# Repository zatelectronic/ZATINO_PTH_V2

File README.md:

<div align="center">

# ZATINO V2 PTH

**Placa de desenvolvimento compatível com Arduino Uno, com componentes através-furo (PTH), programação USB-C via módulo FT232RL**

</div>

---

## 📋 Índice

- [ZATINO V2 PTH](#zatino-v2-pth)
  - [📋 Índice](#-índice)
  - [Visão Geral](#visão-geral)
  - [Renders 3D](#renders-3d)
  - [Diferenças em relação ao ZATINO SMD V2](#diferenças-em-relação-ao-zatino-smd-v2)
  - [Funcionalidades](#funcionalidades)
  - [Especificações Técnicas](#especificações-técnicas)
  - [Lista de Materiais](#lista-de-materiais)
  - [Arquitetura de Alimentação](#arquitetura-de-alimentação)
  - [Compatibilidade de Pinos](#compatibilidade-de-pinos)
  - [Estrutura do Repositório](#estrutura-do-repositório)
  - [Como Usar](#como-usar)
    - [Abrindo no KiCad](#abrindo-no-kicad)
    - [Programando a Placa](#programando-a-placa)
    - [Dica de Montagem](#dica-de-montagem)
  - [Sobre](#sobre)

---

## Visão Geral

**ZATINO V2 PTH** é uma placa de desenvolvimento personalizada, compatível com Arduino Uno, projetada pela **ZAT ELECTRONIC** utilizando o **KICAD 10**. Diferente da versão SMD, esta placa utiliza exclusivamente **componentes através-furo (PTH — Pin Through Hole)**, tornando-a ideal para montagem manual, prototipagem, aprendizado e laboratórios maker.

O microcontrolador principal é o clássico **ATmega328P-PU** no encapsulamento **DIP-28**, encaixado diretamente na placa. A programação é feita via **USB-C** através do módulo **FT232RL**, conectado a um conector fêmea de 6 pinos na borda da placa.

> 💡 Esta placa mantém **total compatibilidade de pinos com o Arduino Uno R3**, permitindo o uso de shields e bibliotecas existentes sem qualquer modificação.

---

## Renders 3D

<div align="center">

*Vista superior — componentes PTH, LEDs coloridos e serigrafia*

<br/>

*Vista isométrica — ATmega328P-PU DIP-28, módulo FT232RL USB-C e montagem geral*

</div>

---

## Diferenças em relação ao ZATINO SMD V2

| Característica | ZATINO V2 PTH | ZATINO SMD V2 |
|----------------|--------------|--------------|
| **Microcontrolador** | ATmega328P-PU (DIP-28) | ATmega328PB-AU (TQFP-32) |
| **Tipo de componentes** | Através-furo (PTH) | Montagem superficial (SMD) |
| **LEDs** | 5mm PTH (vermelho e azul) | SMD 1210 |
| **Resistores** | Axial 0,5W PTH | SMD 1206 |
| **Capacitores** | Eletrolítico + Disco cerâmico PTH | SMD 0805 |
| **Cristal** | PTH HC-49 | SMD HC-49/SD |
| **Montagem** | Manual / Soldagem fácil | Reflow / Soldagem SMD |
| **Público alvo** | Iniciantes, makers, laboratório | Produção, compacto, profissional |

---

## Funcionalidades

- ✅ **ATmega328P-PU** — encapsulamento DIP-28 PTH, 100% compatível com Arduino Uno
- ✅ **Programação via USB-C** pelo módulo FT232RL (conector plugável)
- ✅ **Duplo regulador de tensão** — 5V (AMS1117-5.0) e 3,3V (AMS1117-3.3)
- ✅ **Proteção contra inversão de polaridade** via diodo 1N4007 PTH na entrada de alimentação
- ✅ **Oscilador a cristal de 16 MHz** (encapsulamento PTH HC-49)
- ✅ **Pinout completo Arduino Uno R3** — conectores Digital, Analógico, Alimentação e ICSP
- ✅ **LED vermelho e LED azul** (5mm PTH) para sinalização de status
- ✅ **Botão de reset tátil** (THT 6×6×5 mm)
- ✅ **Entrada de alimentação Barrel Jack (P4)** com chave integrada
- ✅ **Todos os componentes PTH** — ideal para soldagem manual e aprendizado
- ✅ **Projetado com KICAD 10** — EDA totalmente open source
- ✅ **Logotipo Open Source Hardware** na PCB

---

## Especificações Técnicas

| Parâmetro | Valor |
|-----------|-------|
| **Microcontrolador** | ATmega328P-PU (DIP-28) |
| **Velocidade de Clock** | 16 MHz (cristal externo PTH) |
| **Tensão de Operação** | 5V |
| **Tensão de Entrada** | 7–12V (Barrel Jack P4) |
| **Saída 3,3V** | AMS1117-3.3 (até 800mA) |
| **Regulador 5V** | AMS1117-5.0 |
| **Interface USB** | USB-C via módulo FT232RL |
| **Pinos Digital I/O** | 14 (D0–D13), PWM em D3, D5, D6, D9, D10, D11 |
| **Entradas Analógicas** | 6 (A0–A5) |
| **Memória Flash** | 32 KB (ATmega328P) |
| **SRAM** | 2 KB |
| **EEPROM** | 1 KB |
| **Tipo de Montagem** | PTH — Através-furo |
| **Ferramenta de Projeto** | KICAD 10.0 |
| **Versão da PCB** | V2 — 2025 |
| **Fator de Forma** | Compatível com Arduino Uno R3 |

---

## Lista de Materiais

| Ref | Componente | Valor / Parte | Encapsulamento |
|-----|-----------|--------------|----------------|
| MICROCONTROLADOR1 | Microcontrolador | ATmega328P-PU | DIP-28 PTH |
| REGULADOR_5V1 | Regulador de Tensão 5V | AMS1117-5.0 | SOT-223 |
| REGULADOR_3V3 | Regulador de Tensão 3,3V | AMS1117-3.3 | SOT-223 |
| 16MHZ1 | Oscilador a Cristal | 16 MHz | HC-49 PTH |
| BARRA_DE_PINO2 | Conector FTDI | FT232RL USB-C | Fêmea 6 pinos 2,54mm |
| A2 | Referência de Pinout | Arduino Uno R3 | — |
| D1 | Diodo Retificador | 1N4007 | PTH Axial |
| L1 | LED de Status | LED 5mm Vermelho | PTH 5mm |
| L2 | LED de Status | LED 5mm Azul | PTH 5mm |
| R1 | Resistor de LED | 470Ω | Axial 0,5W PTH |
| R2 | Resistor de LED | 220Ω | Axial 0,5W PTH |
| R3 | Resistor de Pull-up | 10KΩ | Axial 0,5W PTH |
| C1, C2, C3 | Capacitores Eletrolíticos | 10µF / 50V | PTH 5×11mm |
| C4, C5 | Capacitores de Cristal | 22pF | Disco Cerâmico PTH |
| C6, C7 | Capacitores de Bypass | 100nF | Disco Cerâmico PTH |
| CONECTOR1 | Conector de Alimentação DC | Barrel Jack P4 | PTH Horizontal |
| BARRA_DE_PINO1 | Conector Auxiliar | 2 terminais | PTH 2,54mm |
| TACTIL_SWITCH1 | Botão de Reset | 6×6×5mm | THT Tátil |
| TP1 | Ponto de Teste | — | PTH |

---

## Arquitetura de Alimentação

```
VIN (Barrel Jack P4)
        │
    [1N4007]  ← Proteção contra inversão de polaridade
        │
   ┌────┴────┐
   │         │
[AMS1117-5.0]  [AMS1117-3.3]
   │         │
  +5V       +3,3V
   │
[ATmega328P-PU DIP-28]
   │
[FT232RL USB-C] ← UART TX/RX + DTR (auto-reset)
```

A placa suporta duas fontes de alimentação:
- **Barrel Jack (P4)** — entrada de 7 a 12V DC, regulada para 5V e 3,3V internamente
- **USB-C via módulo FT232RL** — 5V direto do USB, alimentando o rail VCC quando conectado

---

## Compatibilidade de Pinos

A placa expõe o **pinout completo do Arduino Uno R3**:

| Conector | Pinos |
|----------|-------|
| Digital (PWM) | D0–D13, com PWM em ~3, ~5, ~6, ~9, ~10, ~11 |
| Entradas Analógicas | A0–A5 |
| Alimentação | VIN, 5V, 3V3, GND, AREF, IOREF, RESET |
| ICSP | MISO, MOSI, SCK, RESET, VCC, GND |
| UART (FT232RL) | TX, RX (via conector BARRA_DE_PINO2) |
| I2C | SDA (A4), SCL (A5) |

---

## Estrutura do Repositório

```
ZATINO_PTH_V2/
├── ZATINO_PTH_V2.kicad_pro       # Arquivo de projeto KiCad
├── ZATINO_PTH_V2.kicad_sch       # Esquemático (KICAD 10)
├── ZATINO_PTH_V2.kicad_pcb       # Layout da PCB (KICAD 10)
├── ZATINO_PTH_V2.kicad_prl       # Configurações locais do projeto
├── packages3D/                   # Modelos 3D arquivados (STEP / WRL)
│   ├── atmega328.STEP
│   ├── AMS1117_3V3_axisY.step
│   ├── AMS1117_5V_axisY.step
│   ├── Waveshare_FT232RL_USB-C.step
│   ├── Cristal 16MHz.STEP
│   ├── LED 5mm Red.step
│   ├── LED 5mm Blue.step
│   ├── Diodo 1N4007.STEP
│   └── ...
├── fp-info-cache                 # Cache de footprints
├── fabrication-toolkit-options.json
├── imagem_1.png                  # Render superior da PCB
├── imagem_2.png                  # Render isométrico da PCB
└── README.md
```

---

## Como Usar

### Abrindo no KiCad

1. Instale o **KICAD 10.0** ou superior
2. Clone este repositório:
   ```bash
   git clone https://github.com/seu-usuario/ZATINO_PTH_V2.git
   ```
3. Abra o arquivo `ZATINO_PTH_V2.kicad_pro` no KiCad

### Programando a Placa

1. Encaixe o **módulo FT232RL USB-C** no conector de 6 pinos (`BARRA_DE_PINO2`)
2. Conecte via USB-C ao computador
3. Abra o **Arduino IDE** ou **PlatformIO**
4. Selecione a placa: **Arduino Uno**
5. Selecione a porta COM correta e faça o upload do sketch

### Dica de Montagem

> 🔧 Por ser totalmente PTH, a placa pode ser soldada com ferro de solda convencional. Recomenda-se seguir a ordem: componentes baixos primeiro (resistores, diodo, cristal), depois capacitores, reguladores, soquete DIP-28 e por último os conectores e LEDs.

---

## Sobre

<div align="center">

Projetado por **ZAT ELECTRONIC**

*ZATINO V2 PTH — 2025*

</div>

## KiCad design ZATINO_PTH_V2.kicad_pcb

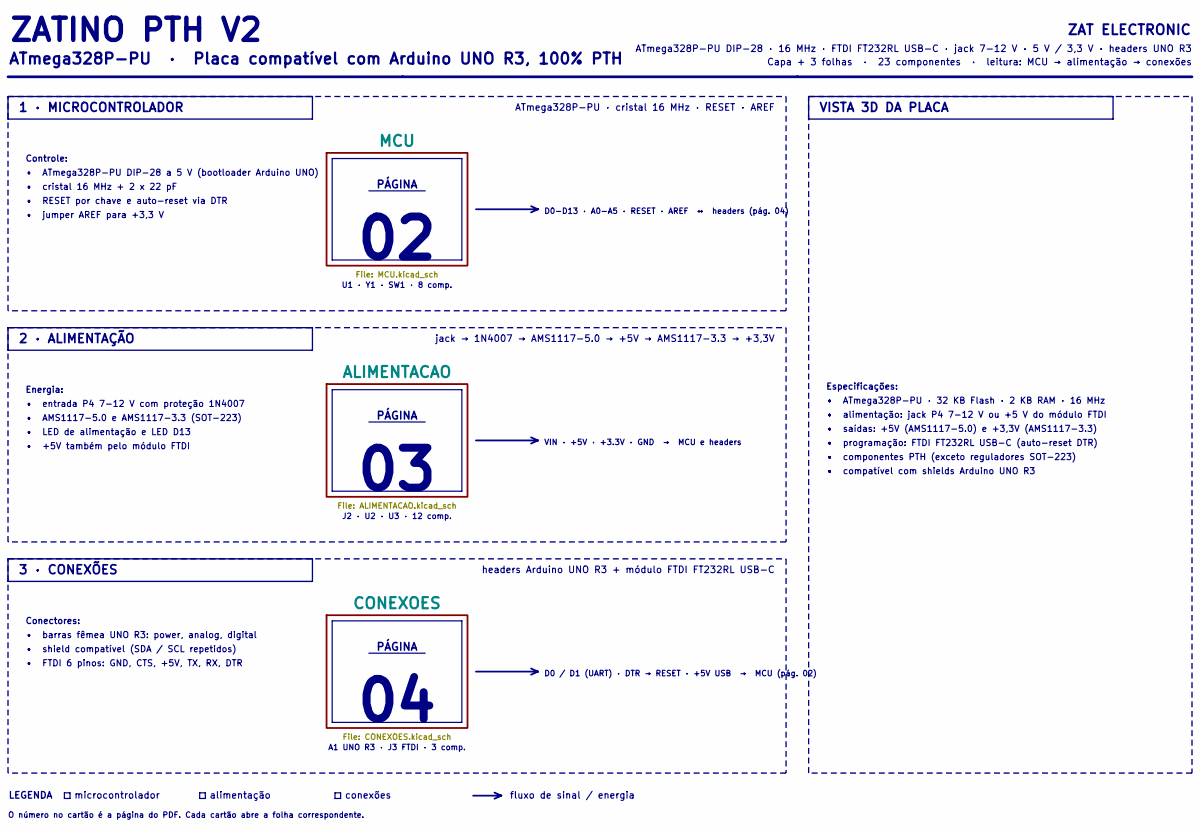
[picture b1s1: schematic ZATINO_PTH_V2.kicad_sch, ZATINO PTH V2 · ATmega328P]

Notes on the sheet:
ZAT ELECTRONIC
Especificações:
• RESET por chave e auto-reset via DTR
D0 / D1 (UART) · DTR → RESET · +5V USB → MCU (pág. 02)
• shield compatível (SDA / SCL repetidos)
J2 · U2 · U3 · 12 comp.
PÁGINA
3 · CONEXÕES
ATmega328P-PU · cristal 16 MHz · RESET · AREF
fluxo de sinal / energia
• +5V também pelo módulo FTDI
conexões
microcontrolador
LEGENDA
Controle:
• barras fêmea UNO R3: power, analog, digital
• jumper AREF para +3,3 V
• LED de alimentação e LED D13
A1 UNO R3 · J3 FTDI · 3 comp.
• cristal 16 MHz + 2 x 22 pF
O número no cartão é a página do PDF. Cada cartão abre a folha correspondente.
• ATmega328P-PU · 32 KB Flash · 2 KB RAM · 16 MHz
• AMS1117-5.0 e AMS1117-3.3 (SOT-223)
ATmega328P-PU · Placa compatível com Arduino UNO R3, 100% PTH
alimentação
• FTDI 6 pinos: GND, CTS, +5V, TX, RX, DTR
• componentes PTH (exceto reguladores SOT-223)
• saídas: +5V (AMS1117-5.0) e +3,3V (AMS1117-3.3)
1 · MICROCONTROLADOR
D0-D13 · A0-A5 · RESET · AREF ↔ headers (pág. 04)
ATmega328P-PU DIP-28 · 16 MHz · FTDI FT232RL USB-C · jack 7-12 V · 5 V / 3,3 V · headers UNO R3
Capa + 3 folhas · 23 componentes · leitura: MCU → alimentação → conexões
• programação: FTDI FT232RL USB-C (auto-reset DTR)
• alimentação: jack P4 7-12 V ou +5 V do módulo FTDI
VISTA 3D DA PLACA
Conectores:
Energia:
U1 · Y1 · SW1 · 8 comp.
ZATINO PTH V2
VIN · +5V · +3.3V · GND → MCU e headers

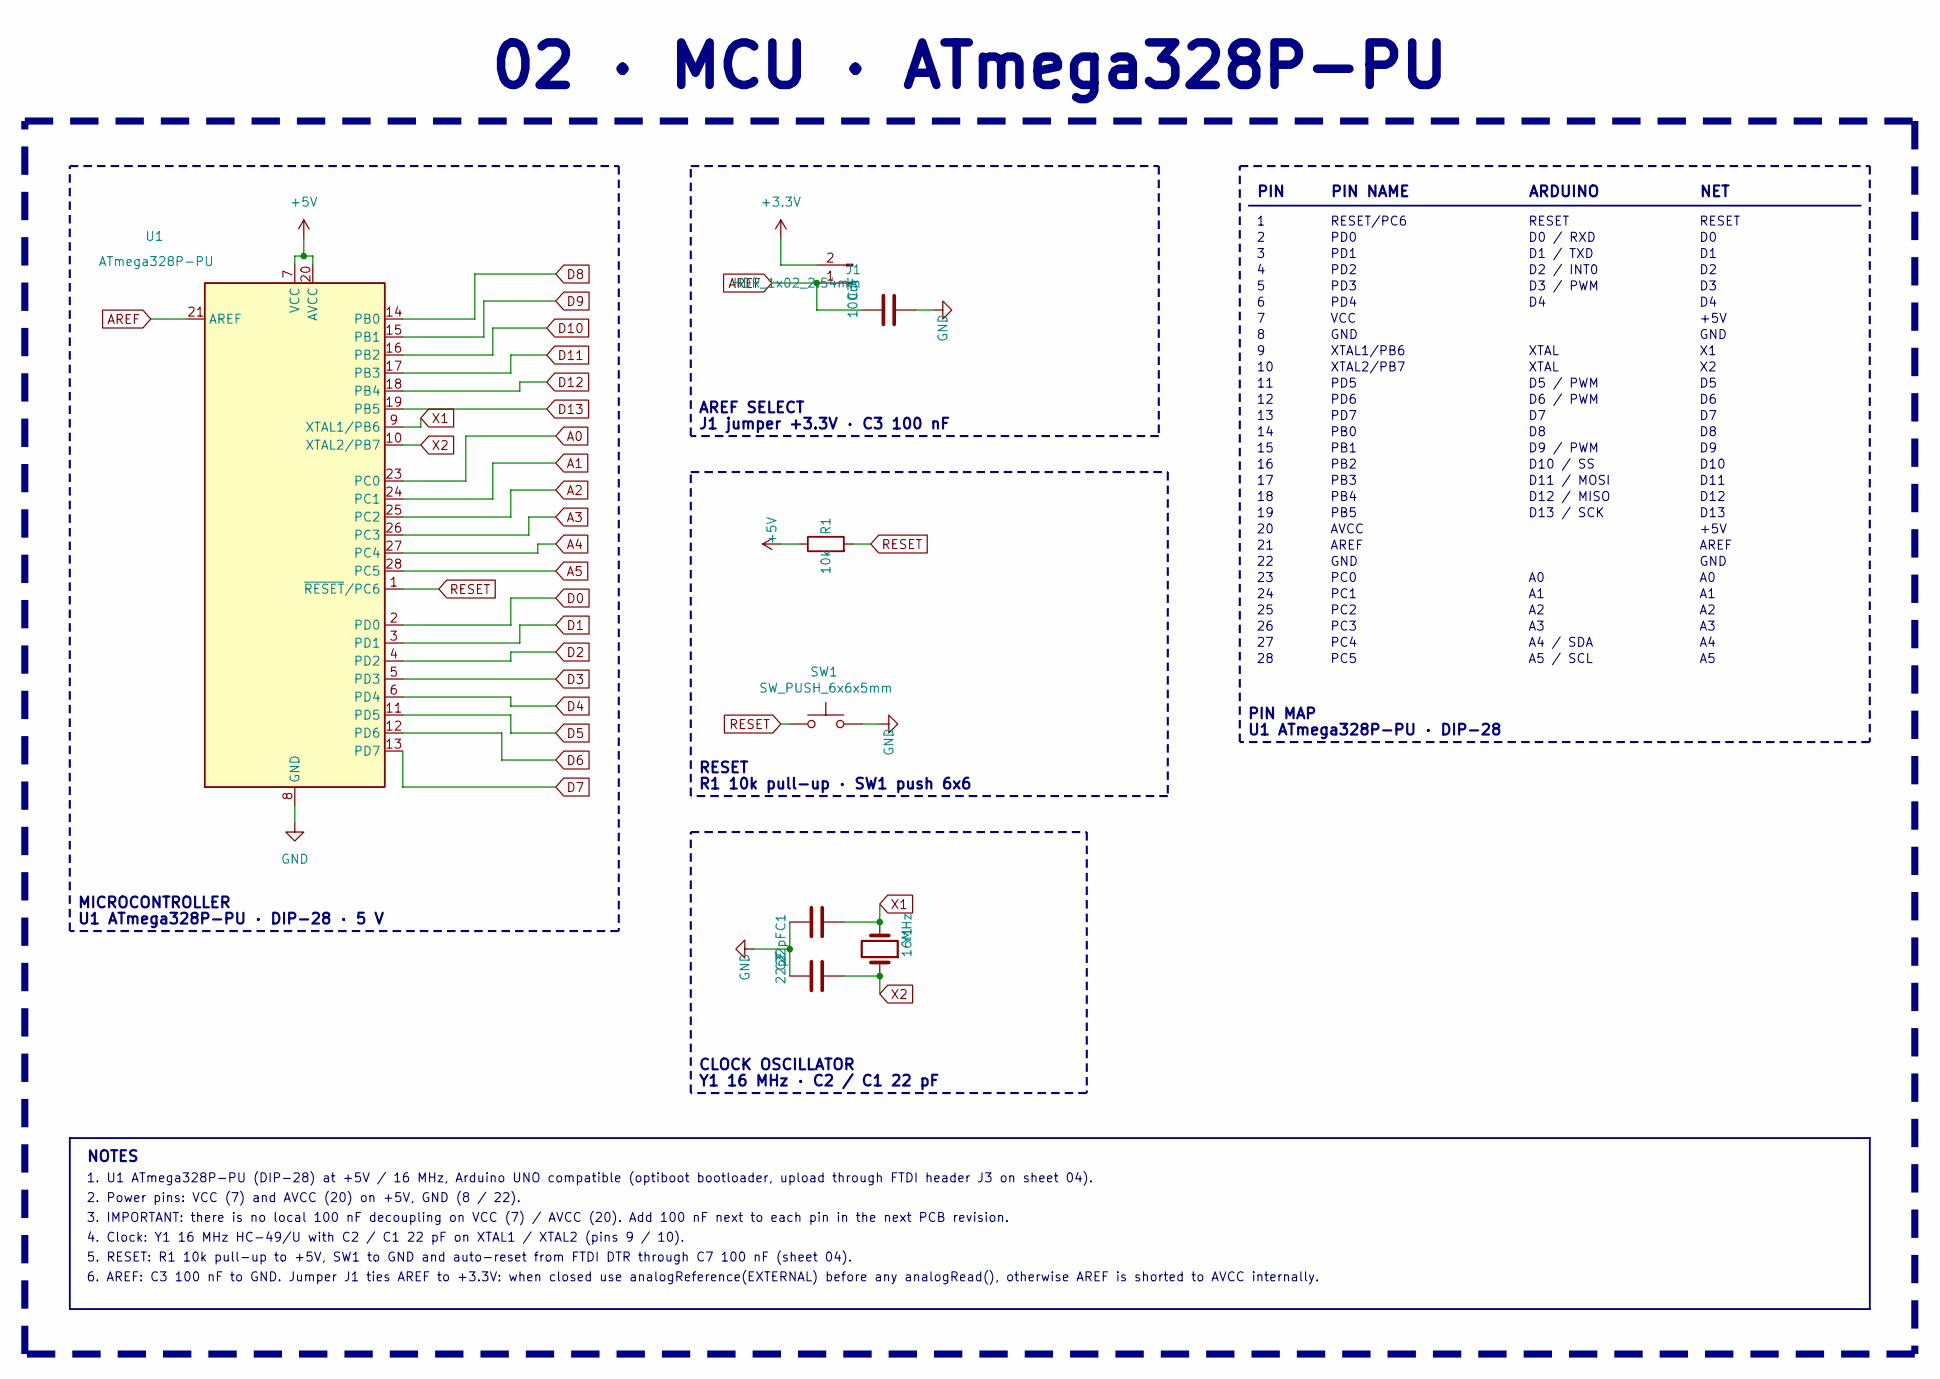
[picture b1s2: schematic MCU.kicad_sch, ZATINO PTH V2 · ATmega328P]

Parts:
C1, C2: 22pF; C_Disc_D3.0mm_W1.6mm_P2.50mm_22pF
C3: 100nF; C_Disc_D3.0mm_W2.0mm_P2.50mm_100nF
J1: HDR_1x02_2.54mm; PinHeader_1x02_P2.54mm_Vertical
R1: 10k; R_Axial_DIN0204_L3.6mm_D1.6mm_P7.62mm_Horizontal_10K
SW1: SW_PUSH_6x6x5mm; SW_PUSH_6mm_H5mm
U1: ATmega328P-PU; DIP-28_W7.62mm_ATmega328P-PU
Y1: 16MHz; Crystal_HC18-U_Vertical_16MHz

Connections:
+3.3V: J1.2; also elsewhere on the board
+5V: R1.1, U1.7 (VCC), U1.20 (AVCC); also elsewhere on the board
A0: U1.23 (PC0); also elsewhere on the board
A1: U1.24 (PC1); also elsewhere on the board
A2: U1.25 (PC2); also elsewhere on the board
A3: U1.26 (PC3); also elsewhere on the board
A4: U1.27 (PC4); also elsewhere on the board
A5: U1.28 (PC5); also elsewhere on the board
AREF: C3.2, J1.1, U1.21 (AREF); also elsewhere on the board
D0: U1.2 (PD0); also elsewhere on the board
D1: U1.3 (PD1); also elsewhere on the board
D2: U1.4 (PD2); also elsewhere on the board
D3: U1.5 (PD3); also elsewhere on the board
D4: U1.6 (PD4); also elsewhere on the board
D5: U1.11 (PD5); also elsewhere on the board
D6: U1.12 (PD6); also elsewhere on the board
D7: U1.13 (PD7); also elsewhere on the board
D8: U1.14 (PB0); also elsewhere on the board
D9: U1.15 (PB1); also elsewhere on the board
D10: U1.16 (PB2); also elsewhere on the board
D11: U1.17 (PB3); also elsewhere on the board
D12: U1.18 (PB4); also elsewhere on the board
D13: U1.19 (PB5); also elsewhere on the board
GND: C1.2, C2.2, C3.1, SW1.2, U1.8 (GND), U1.22 (GND); also elsewhere on the board
RESET: R1.2, SW1.1, U1.1 (~RESET/PC6); also elsewhere on the board
X1: C1.1, U1.9 (XTAL1/PB6), Y1.2
X2: C2.1, U1.10 (XTAL2/PB7), Y1.1

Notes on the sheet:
GND
D13
AREF SELECT
PD4
D6 / PWM
D3 / PWM
AREF
PD2
PD1
RESET
CLOCK OSCILLATOR
PD7
RESET/PC6
XTAL1/PB6
D2 / INT0
A5 / SCL
D12 / MISO
02 · MCU · ATmega328P-PU
D5 / PWM
+5V
XTAL2/PB7
D9 / PWM
XTAL
3. IMPORTANT: there is no local 100 nF decoupling on VCC (7) / AVCC (20). Add 100 nF next to each pin in the next PCB revision.
PB3
PC4
PIN NAME
PIN MAP
PC3
5. RESET: R1 10k pull-up to +5V, SW1 to GND and auto-reset from FTDI DTR through C7 100 nF (sheet 04).
2. Power pins: VCC (7) and AVCC (20) on +5V, GND (8 / 22).
D13 / SCK
PC1
A4 / SDA
NOTES
ARDUINO
VCC
D10
PD6
D1 / TXD

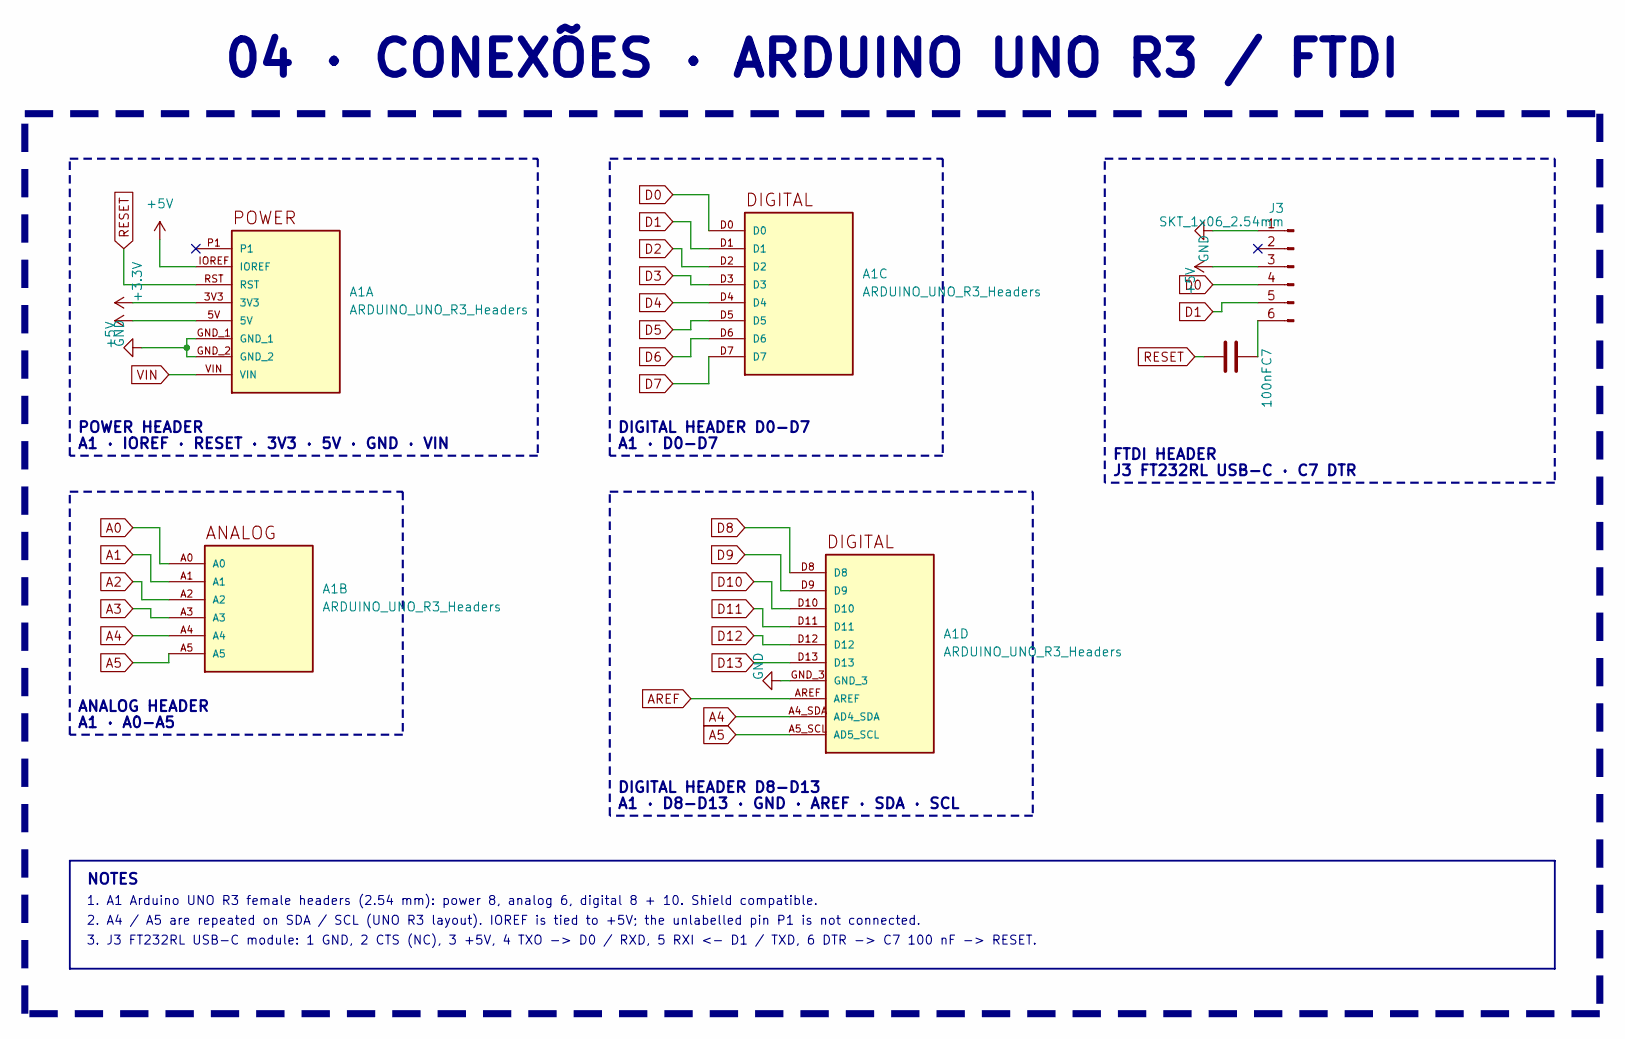
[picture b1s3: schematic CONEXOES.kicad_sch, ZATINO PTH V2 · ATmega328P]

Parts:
A1: ARDUINO_UNO_R3_Headers
C7: 100nF; C_Disc_D3.0mm_W2.0mm_P2.50mm_100nF
J3: SKT_1x06_2.54mm; PinSocket_1x06_P2.54mm_Vertical_FT232RL_USB-C

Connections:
+3.3V: A1.3V3; also elsewhere on the board
+5V: A1.5V, A1.IOREF, J3.3; also elsewhere on the board
A0: A1.A0; also elsewhere on the board
A1: A1.A1; also elsewhere on the board
A2: A1.A2; also elsewhere on the board
A3: A1.A3; also elsewhere on the board
A4: A1.A4, A1.A4_SDA (AD4_SDA); also elsewhere on the board
A5: A1.A5, A1.A5_SCL (AD5_SCL); also elsewhere on the board
AREF: A1.AREF; also elsewhere on the board
D0: A1.D0, J3.4; also elsewhere on the board
D1: A1.D1, J3.5; also elsewhere on the board
D2: A1.D2; also elsewhere on the board
D3: A1.D3; also elsewhere on the board
D4: A1.D4; also elsewhere on the board
D5: A1.D5; also elsewhere on the board
D6: A1.D6; also elsewhere on the board
D7: A1.D7; also elsewhere on the board
D8: A1.D8; also elsewhere on the board
D9: A1.D9; also elsewhere on the board
D10: A1.D10; also elsewhere on the board
D11: A1.D11; also elsewhere on the board
D12: A1.D12; also elsewhere on the board
D13: A1.D13; also elsewhere on the board
GND: A1.GND_1, A1.GND_2, A1.GND_3, J3.1; also elsewhere on the board
unnamed: C7.1, J3.6
RESET: A1.RST, C7.2; also elsewhere on the board
VIN: A1.VIN; also elsewhere on the board

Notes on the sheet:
POWER HEADER
J3 FT232RL USB-C · C7 DTR
A1 · D0-D7
DIGITAL HEADER D8-D13
ANALOG HEADER
DIGITAL HEADER D0-D7
FTDI HEADER
A1 · D8-D13 · GND · AREF · SDA · SCL
A1 · IOREF · RESET · 3V3 · 5V · GND · VIN
A1 · A0-A5
04 · CONEXÕES · ARDUINO UNO R3 / FTDI
1. A1 Arduino UNO R3 female headers (2.54 mm): power 8, analog 6, digital 8 + 10. Shield compatible.
NOTES
3. J3 FT232RL USB-C module: 1 GND, 2 CTS (NC), 3 +5V, 4 TXO -> D0 / RXD, 5 RXI <- D1 / TXD, 6 DTR -> C7 100 nF -> RESET.
2. A4 / A5 are repeated on SDA / SCL (UNO R3 layout). IOREF is tied to +5V; the unlabelled pin P1 is not connected.

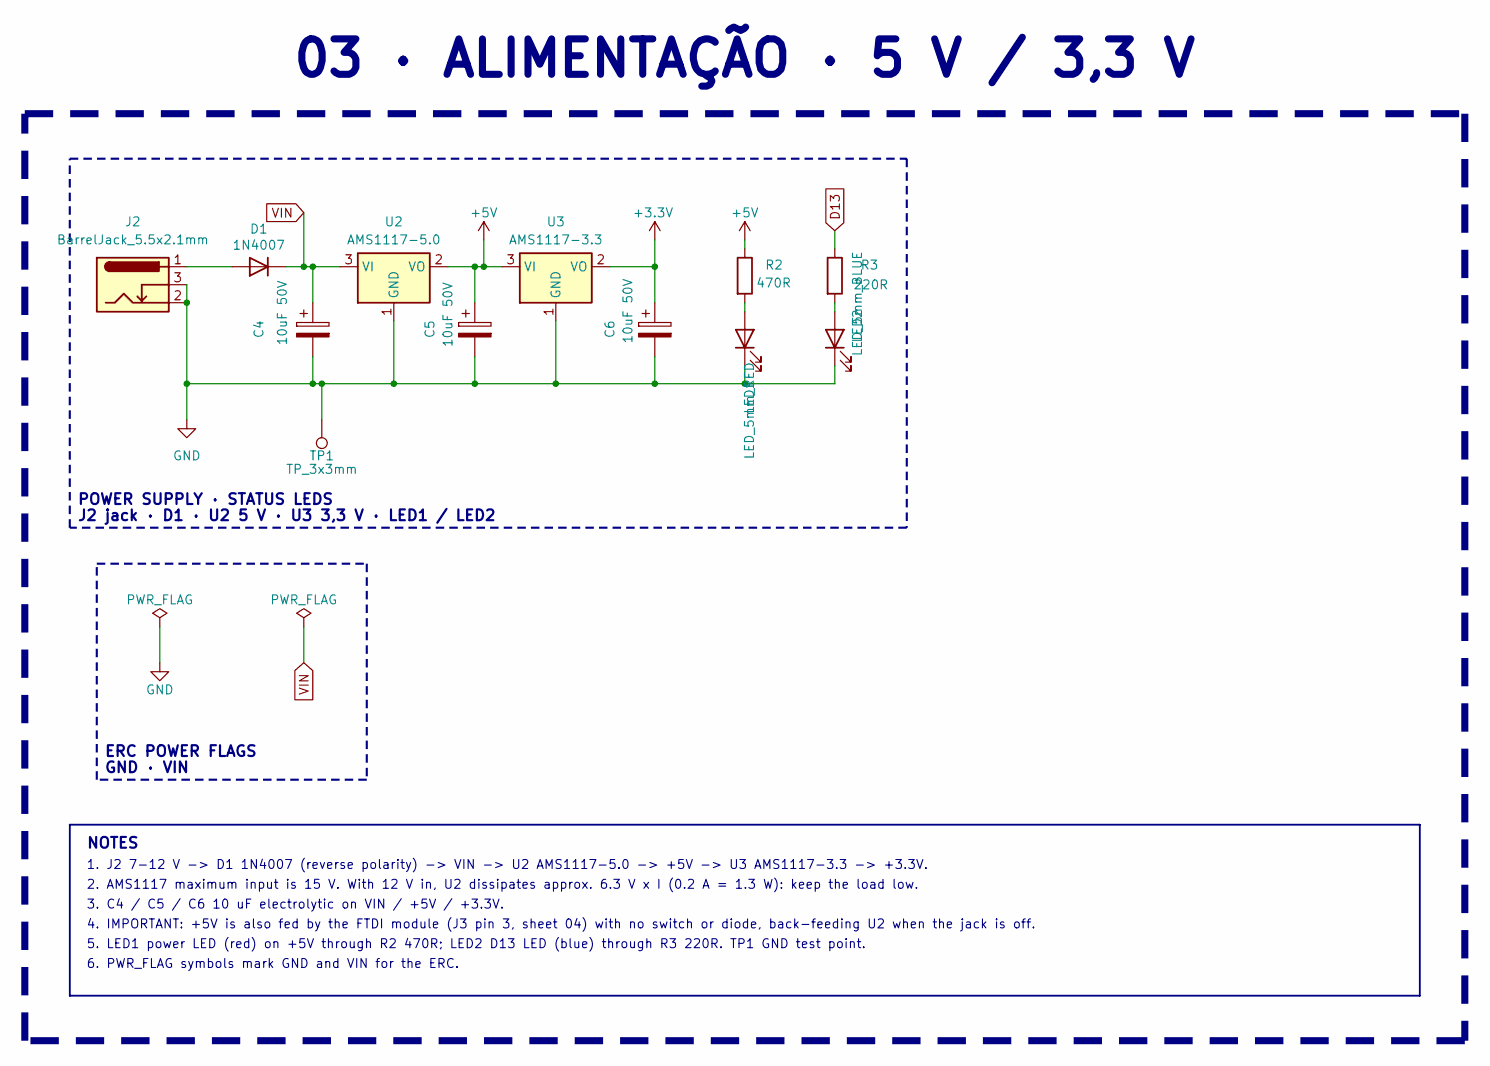
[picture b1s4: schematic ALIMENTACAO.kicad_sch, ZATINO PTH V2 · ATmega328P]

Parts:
C4, C5, C6: 10uF 50V; CP_Radial_D5.0mm_P2.50mm_10uF_50V
D1: 1N4007; D_DO-41_SOD81_P10.16mm_Horizontal_1N4007
J2: BarrelJack_5.5x2.1mm; BarrelJack_Horizontal_EdgeMount
LED1: LED_5mm_RED; LED_D5.0mm_Red
LED2: LED_5mm_BLUE; LED_D5.0mm_Blue
R2: 470R; R_Axial_DIN0204_L3.6mm_D1.6mm_P7.62mm_Horizontal_470R
R3: 220R; R_Axial_DIN0204_L3.6mm_D1.6mm_P7.62mm_Horizontal_220R
TP1: TP_3x3mm; TestPoint_Pad_3.0x3.0mm
U2: AMS1117-5.0; SOT-223-3_TabPin2_AMS1117-5.0
U3: AMS1117-3.3; SOT-223-3_TabPin2_AMS1117-3.3

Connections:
+3.3V: C6.1, U3.2 (VO); also elsewhere on the board
+5V: C5.1, R2.1, U2.2 (VO), U3.3 (VI); also elsewhere on the board
D13: R3.1; also elsewhere on the board
GND: C4.2, C5.2, C6.2, J2.2, J2.3, LED1.1 (K), LED2.1 (K), TP1.1 (1_1), U2.1 (GND), U3.1 (GND); also elsewhere on the board
unnamed: D1.2 (A), J2.1
unnamed: LED1.2 (A), R2.2
unnamed: LED2.2 (A), R3.2
VIN: C4.1, D1.1 (K), U2.3 (VI); also elsewhere on the board

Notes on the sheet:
03 · ALIMENTAÇÃO · 5 V / 3,3 V
J2 jack · D1 · U2 5 V · U3 3,3 V · LED1 / LED2
5. LED1 power LED (red) on +5V through R2 470R; LED2 D13 LED (blue) through R3 220R. TP1 GND test point.
3. C4 / C5 / C6 10 uF electrolytic on VIN / +5V / +3.3V.
POWER SUPPLY · STATUS LEDS
GND · VIN
6. PWR_FLAG symbols mark GND and VIN for the ERC.
ERC POWER FLAGS
NOTES
1. J2 7-12 V -> D1 1N4007 (reverse polarity) -> VIN -> U2 AMS1117-5.0 -> +5V -> U3 AMS1117-3.3 -> +3.3V.
2. AMS1117 maximum input is 15 V. With 12 V in, U2 dissipates approx. 6.3 V x I (0.2 A = 1.3 W): keep the load low.
4. IMPORTANT: +5V is also fed by the FTDI module (J3 pin 3, sheet 04) with no switch or diode, back-feeding U2 when the jack is off.

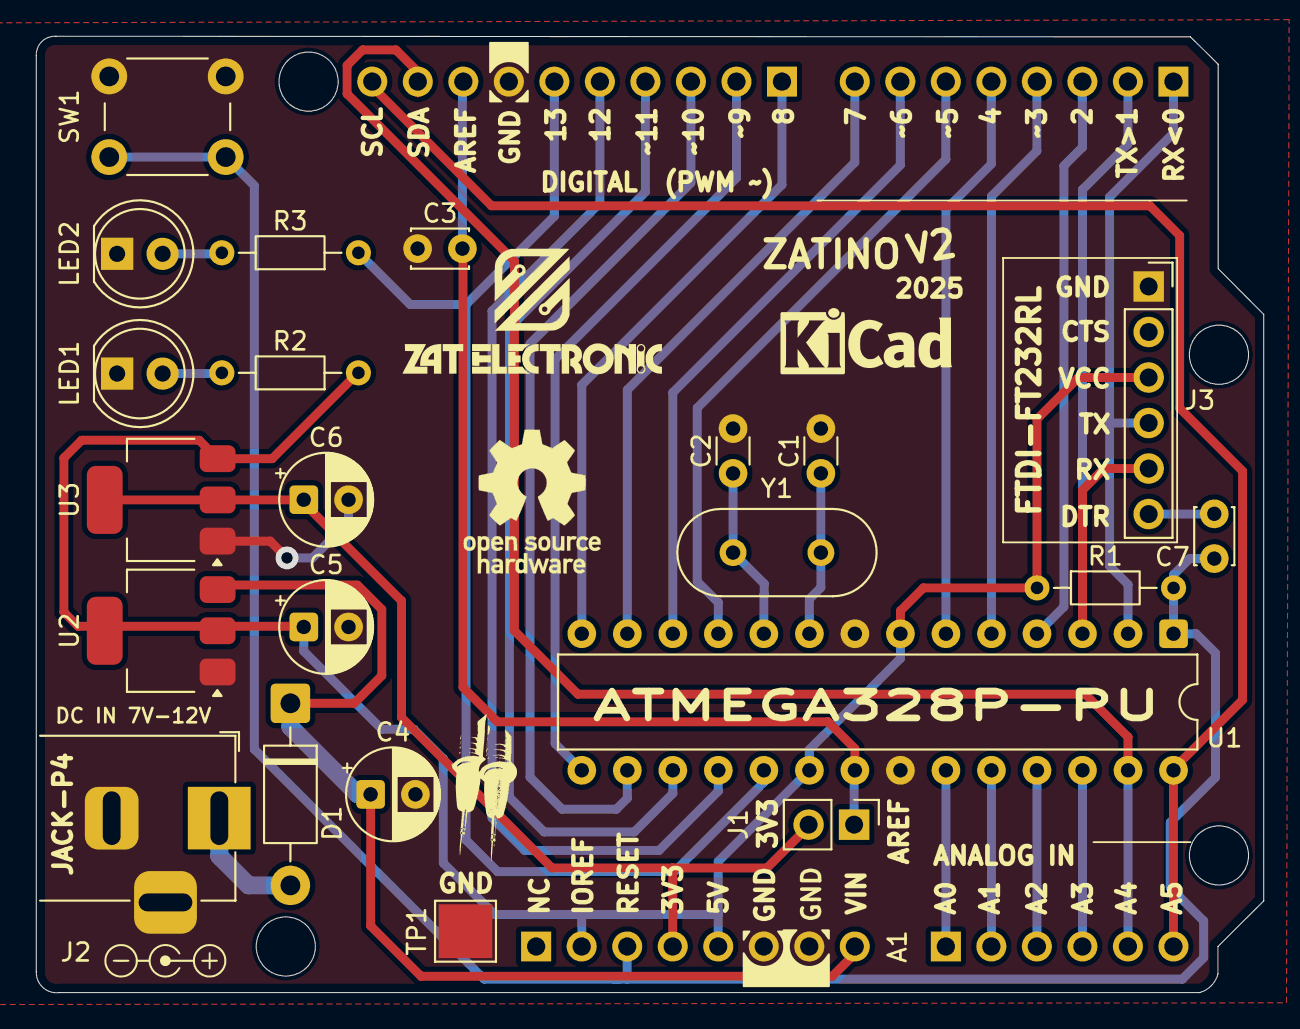
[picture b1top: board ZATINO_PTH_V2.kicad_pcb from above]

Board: 2 copper layers, 68.5 x 53.4 mm, 23 parts (0 on the bottom side), 32 nets.

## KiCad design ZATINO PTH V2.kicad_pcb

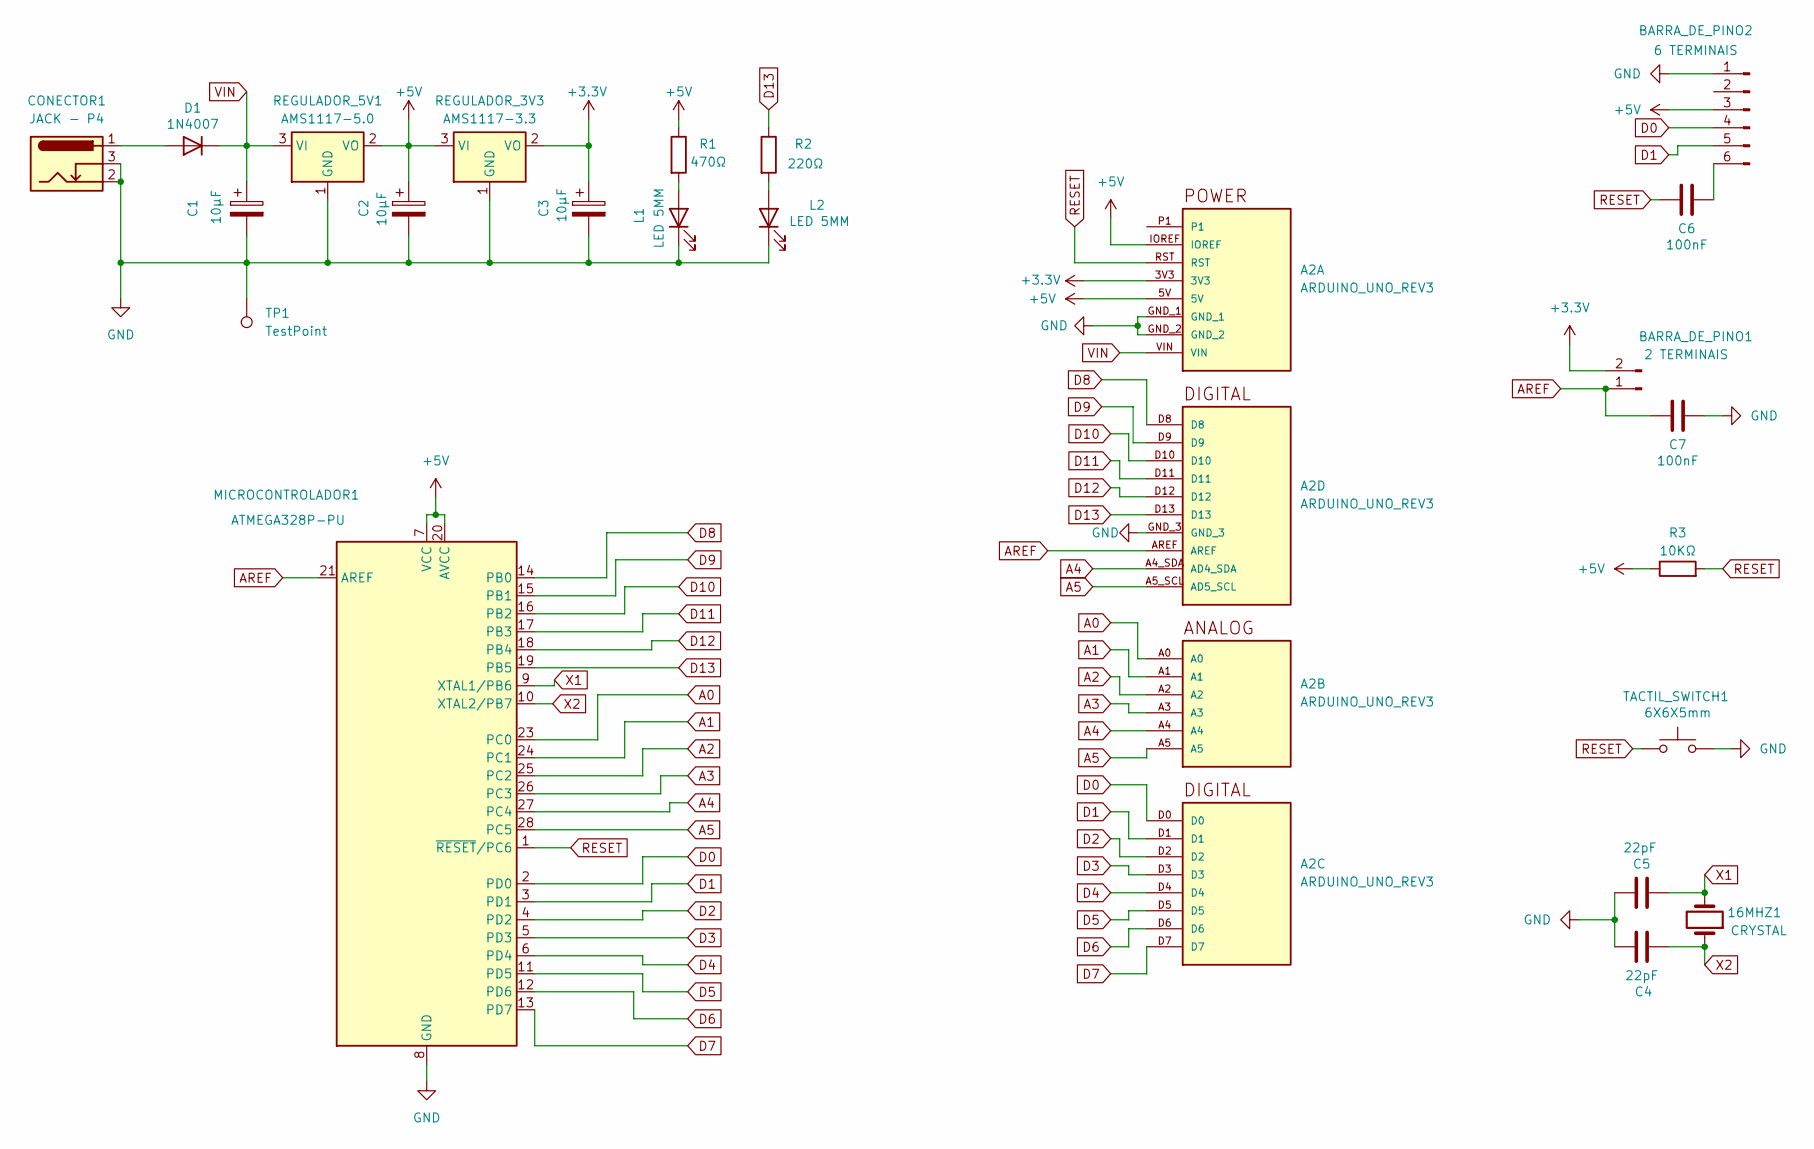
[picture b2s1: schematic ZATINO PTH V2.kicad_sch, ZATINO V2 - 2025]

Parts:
16MHZ1: CRYSTAL; Crystal_HC18-U_Vertical
A2: ARDUINO_UNO_REV3; ARDUINO_ARDUINO_UNO_REV3; PARTREV N/A
BARRA_DE_PINO1: 2 TERMINAIS; PinHeader_1x02_P2.54mm_Vertical
BARRA_DE_PINO2: 6 TERMINAIS; PinHeader_1x06_P2.54mm_Vertical
C1, C2, C3: 10μF; CP_Radial_D5.0mm_P2.50mm
C4, C5: 22pF; C_Disc_D3.0mm_W1.6mm_P2.50mm
C6, C7: 100nF; C_Disc_D3.0mm_W2.0mm_P2.50mm
CONECTOR1: JACK - P4; BarrelJack_Horizontal
D1: 1N4007; D_DO-41_SOD81_P10.16mm_Horizontal
L1, L2: LED 5MM; LED_D5.0mm
MICROCONTROLADOR1: ATMEGA328P-PU; DIP-28_W7.62mm
R1: 470Ω; R_Axial_DIN0204_L3.6mm_D1.6mm_P7.62mm_Horizontal
R2: 220Ω; R_Axial_DIN0204_L3.6mm_D1.6mm_P7.62mm_Horizontal
R3: 10KΩ; R_Axial_DIN0204_L3.6mm_D1.6mm_P7.62mm_Horizontal
REGULADOR_3V3: AMS1117-3.3; SOT-223-3_TabPin2
REGULADOR_5V1: AMS1117-5.0; SOT-223-3_TabPin2
TACTIL_SWITCH1: 6X6X5mm; SW_PUSH_6mm_H5mm
TP1: TestPoint; TestPoint_Pad_3.0x3.0mm

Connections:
+3.3V: A2.3V3, BARRA_DE_PINO1.2, C3.1, REGULADOR_3V3.2 (VO)
+5V: A2.5V, A2.IOREF, BARRA_DE_PINO2.3, C2.1, MICROCONTROLADOR1.7 (VCC), MICROCONTROLADOR1.20 (AVCC), R1.1, R3.1, REGULADOR_3V3.3 (VI), REGULADOR_5V1.2 (VO)
A0: A2.A0, MICROCONTROLADOR1.23 (PC0)
A1: A2.A1, MICROCONTROLADOR1.24 (PC1)
A2: A2.A2, MICROCONTROLADOR1.25 (PC2)
A3: A2.A3, MICROCONTROLADOR1.26 (PC3)
A4: A2.A4, A2.A4_SDA (AD4_SDA), MICROCONTROLADOR1.27 (PC4)
A5: A2.A5, A2.A5_SCL (AD5_SCL), MICROCONTROLADOR1.28 (PC5)
AREF: A2.AREF, BARRA_DE_PINO1.1, C7.2, MICROCONTROLADOR1.21 (AREF)
D0: A2.D0, BARRA_DE_PINO2.4, MICROCONTROLADOR1.2 (PD0)
D1: A2.D1, BARRA_DE_PINO2.5, MICROCONTROLADOR1.3 (PD1)
D2: A2.D2, MICROCONTROLADOR1.4 (PD2)
D3: A2.D3, MICROCONTROLADOR1.5 (PD3)
D4: A2.D4, MICROCONTROLADOR1.6 (PD4)
D5: A2.D5, MICROCONTROLADOR1.11 (PD5)
D6: A2.D6, MICROCONTROLADOR1.12 (PD6)
D7: A2.D7, MICROCONTROLADOR1.13 (PD7)
D8: A2.D8, MICROCONTROLADOR1.14 (PB0)
D9: A2.D9, MICROCONTROLADOR1.15 (PB1)
D10: A2.D10, MICROCONTROLADOR1.16 (PB2)
D11: A2.D11, MICROCONTROLADOR1.17 (PB3)
D12: A2.D12, MICROCONTROLADOR1.18 (PB4)
D13: A2.D13, MICROCONTROLADOR1.19 (PB5), R2.1
GND: A2.GND_1, A2.GND_2, A2.GND_3, BARRA_DE_PINO2.1, C1.2, C2.2, C3.2, C4.2, C5.2, C7.1, CONECTOR1.2, CONECTOR1.3, L1.1 (K), L2.1 (K), MICROCONTROLADOR1.8 (GND), MICROCONTROLADOR1.22 (GND), REGULADOR_3V3.1 (GND), REGULADOR_5V1.1 (GND), TACTIL_SWITCH1.2, TP1.1
unnamed: BARRA_DE_PINO2.6, C6.1
unnamed: CONECTOR1.1, D1.2 (A)
unnamed: L1.2 (A), R1.2
unnamed: L2.2 (A), R2.2
RESET: A2.RST, C6.2, MICROCONTROLADOR1.1 (~RESET/PC6), R3.2, TACTIL_SWITCH1.1
VIN: A2.VIN, C1.1, D1.1 (K), REGULADOR_5V1.3 (VI)
X1: 16MHZ1.2, C5.1, MICROCONTROLADOR1.9 (XTAL1/PB6)
X2: 16MHZ1.1, C4.1, MICROCONTROLADOR1.10 (XTAL2/PB7)

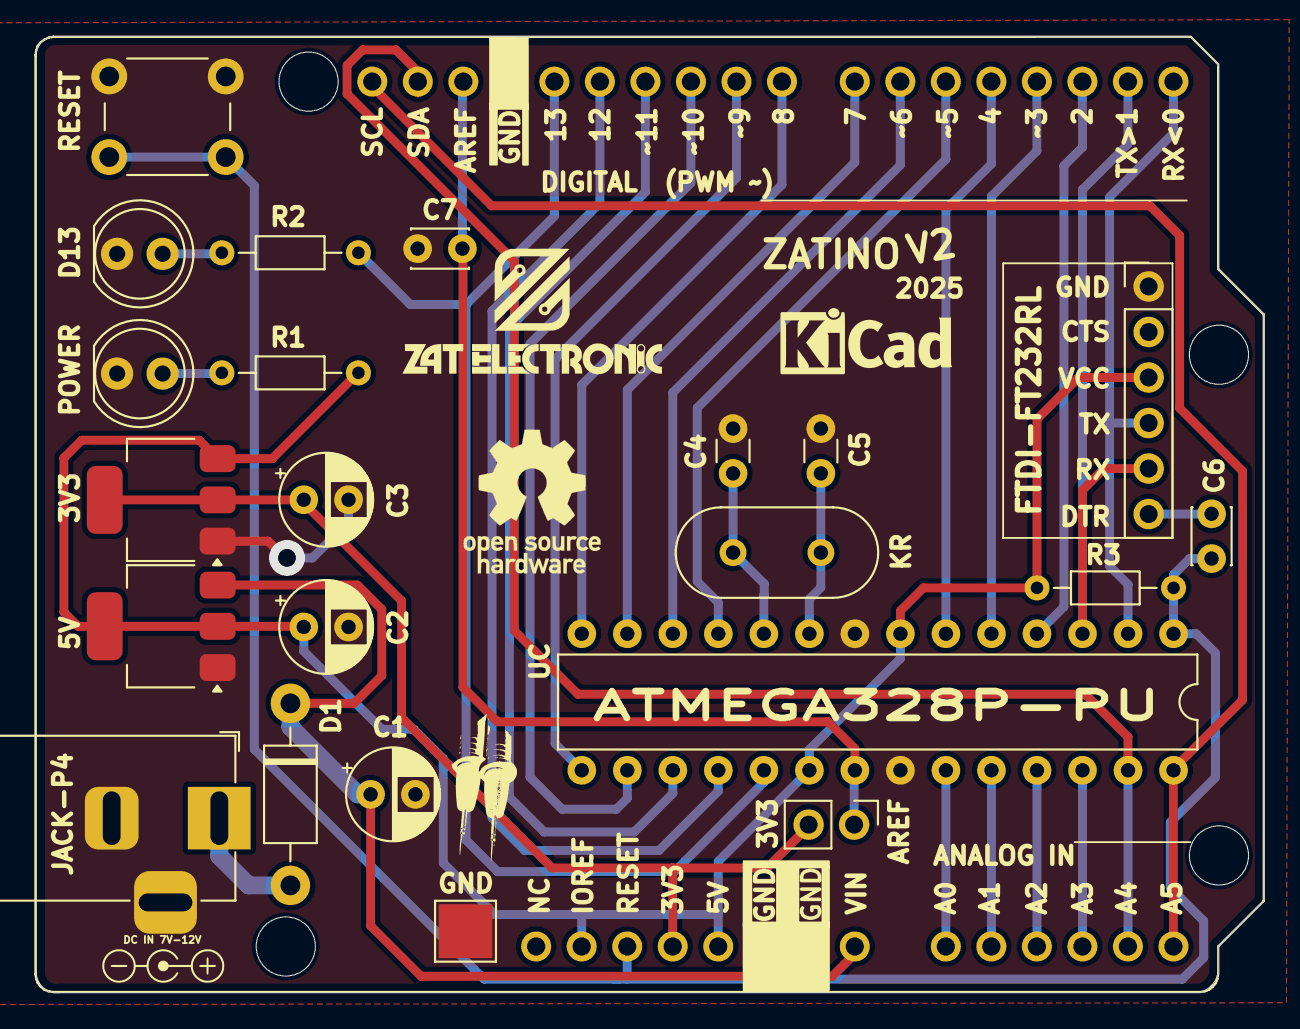
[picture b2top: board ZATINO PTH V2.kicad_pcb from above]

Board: 2 copper layers, 68.5 x 53.4 mm, 23 parts (0 on the bottom side), 32 nets.

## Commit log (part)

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2026-06-28 commit-28-06-2026
2026-06-28 commit_3
2026-06-28 commit-4
2026-06-29 commit-5
2026-06-29 COMMIT-6
2026-06-29 COMMIT-7
2026-06-29 COMMIT-8
